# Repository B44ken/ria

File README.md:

# ria

ria is a small wheeled biped built for jumping and fast ground motion.

### bom

- 2x 5010 260kv bldc
- 2x gbm2804 145kv bldc
- 2x sg90 servo
- 4x as5600
- funfly 1300 4s lipo
- m2, m3 screws
- 6x 693zz bearings (planet gears)
- 2x 687zz bearings (knee sprockets)
- 2x gt3 300 mm closed belt

### specs
- 10:1 two stage knee transmission
- custom pcb
- 100mm upper and lower legs
- 720g mass
  - 150g/side motors, 200g plastic, 150g battery, 70g everything else
- 20cm jump height, 30kmh top speed (tentative, accurate-ish)

# printed parts
ria is built mostly from parts designed in cadquery. nearly every part has a flat face so it should be easy to 3d print. you'll also need some m3 screws of various sizes and a handful of bearings.

```bash
cd models
python3 main.py
```

# pcb
the pcb is the most expensive part of the design, at roughly $100 (from jlcpcb assembly). i built it in backplane. the kicad project is at `pcb/ria.kicad_pro`

# software
ria is trained and driven in [botblocks.dev](https://botblocks.dev)

```bash
cd software
botblocks import robot bot.json --save $MY_FORK/robot
botblocks run drive.py
```

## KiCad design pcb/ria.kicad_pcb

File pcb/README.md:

# pcb

open `ria.kicad_pro` in kicad or backplane. edit `ria.kicad_pcb` and `ria.kicad_sch` directly. the local symbols, footprints, library tables and `3dmodels/` travel with the project; `ts-pcb/` retains the original tscircuit source and generated outputs.

the sensorless revision uses a doit esps3-32-n4 module with 4mb flash, four drv8316ctrgfr motor drivers, an icm-42688-p imu, usb-c data and a vertical xt60 battery input. the four encoder headers and their pullups are removed. two measured phase currents per motor give eight adc channels; the third phase current is reconstructed from their sum. motor phase outputs never connect directly to the mcu.

the schematic has 104 components and 93 connected nets. on 2026-10-14, fresh kicad 10.0.6 checks with refilled zones reported zero erc violations, zero pcb errors, zero unrouted connections and zero schematic mismatches. the independent driver audit passed 288 pin/net assertions, and the saved-file verifier passed. fabrication design rules are unchanged. 39 pcb warnings remain: 20 routing-stub/via warnings and 19 silkscreen overlap, edge or mask-clipping warnings. this is a hardware revision; sensorless firmware, continuous motor-current temperature and bench operation are not verified.

the [layout preview](../build/review/current-sensing-65mm/board.png), native reports and verifier output are in `build/review/current-sensing-65mm/`.

run the native checks with kicad's python, which includes `pcbnew` and `wx`, and `kicad-cli` on the path. on this mac:

```sh
export PATH="/Applications/KiCad/KiCad.app/Contents/MacOS:$PATH"
"/Applications/KiCad/KiCad.app/Contents/Frameworks/Python.framework/Versions/3.9/bin/python3.9" verify-kicad.py
"/Applications/KiCad/KiCad.app/Contents/MacOS/kicad-cli" sch erc ria.kicad_sch --format json --exit-code-violations -o /tmp/ria-erc.json
"/Applications/KiCad/KiCad.app/Contents/MacOS/kicad-cli" pcb drc ria.kicad_pcb --schematic-parity --format json --exit-code-violations -o /tmp/ria-drc.json
```

## current sensing and control

the [ti drv8316c datasheet](https://www.ti.com/lit/ds/symlink/drv8316c.pdf) defines the hardware interface and support parts. each drv8316ct uses three pwm inputs without spi. mode connects through 47kΩ to its own avdd, selecting three-pwm control with analog current outputs. the three low-side input pins connect to local avdd, drvoff and vsel_bk connect to ground, and nsleep uses gpio47 with an external pulldown. slew and ocp/sr connect to ground; gain floats for 0.3v/a. each fault output has its own 5.1kΩ pullup to local avdd and a separate mcu input.

soa and sob pass through 330Ω/22pf filters to adc1 inputs. vref connects to the driver's local avdd, giving a zero-current offset of avdd/2, nominally 1.65v. sample only during valid low-side conduction windows synchronized to pwm; these outputs do not continuously measure phase current through every switching state. the 16a hardware overcurrent threshold protects against faults. firmware must impose the intended 2.8a motor-current target rather than treating that threshold as an operating limit.

| motor | pwm a/b/c gpio | current a/b gpio | fault gpio |
| --- | --- | --- | --- |
| 1 | 13 / 14 / 15 | 4 / 5 | 44 |
| 2 | 16 / 17 / 18 | 1 / 2 | 48 |
| 3 | 21 / 35 / 36 | 6 / 7 | 42 |
| 4 | 37 / 38 / 39 | 8 / 9 | 11 |

imu sda/scl move to gpio40/41; its interrupt remains gpio12. battery sensing uses gpio10, a 100kΩ/20kΩ divider and 100nf bypass, giving 2.8v at a 16.8v battery input. gpio3 remains unused because it is a boot strap. use mcpwm for all twelve motor pwm outputs; ledc has eight channels.

each driver has a 47nf 50v charge-pump flying capacitor, 1µf charge-pump reservoir, two 100nf vm bypasses and 10µf 50v local bulk capacitance. local avdd uses a 1µf 50v x7r 0805 capacitor, c28323, selected for ti's effective 0.7–1.3µf requirement at 3.3v. vref shares that bypass; the optional extra capacitor is omitted. each hardware variant's buck converter uses 22Ω from sw_bk to fb_bk and a 22µf 25v 0805 output capacitor. its unloaded output and avdd remain private to that driver, separate from the board's 3.3v supply.

## layout and connectors

the board is 50×65mm, with four copper layers and nominal 1.6mm thickness. components mount on top. the inner layers provide ground and battery distribution; the antenna keepout covers all four copper layers, and the top notch removes pcb material from beneath the antenna. the nominal stackup uses jlc04161h-7628, with 35µm outer and 15.2µm inner copper.

the power connector is a vertical amass xt60pb-m.g.y, c19268037, with its mating face above the board. the [manufacturer drawing](https://www.china-amass.net/uploads/62.XT60PB-M-SPEC-2025V0.pdf) specifies a 15.5×8.1mm housing, 16mm height above the pcb, 7.2mm pin pitch and two 4.6mm pcb holes. the imported footprint was corrected to that drawing; pad 1 is ground and pad 2 is battery. its included 3d model is a simplified housing envelope, not the manufacturer's detailed model.

usb-c is at the bottom centre. the outward-facing motor headers sit at x=78.5/121.5mm, y=91mm, shifted down 2mm to clear the upright xt60. they use 5.08mm-pitch wj2edgr-5.08-03p-14-00a headers, c70914, with 1.7mm drills and 3mm lands. mating wire plugs are wj2edgk-5.08-03p-14-00a, c71371; these are not included in the pcb bom. their housings have no included 3d model, so fit uses the manufacturer's drawing and footprint fabrication outlines. the other two motors use mirrored a/b/c socket columns at 8mm pitch.

the mcu is doit esps3-32-n4, c49164655. its [manufacturer pin table and land drawing](https://atta.szlcsc.com/upload/public/pdf/source/20250610/5E546491D868C5B4673AE97C7A2DC844.pdf) define the module footprint. the ground stencil uses nine 0.9mm openings at 1.4mm pitch with twelve thermal holes between them. the existing wroom model represents its approximate 18×25.5mm envelope. the drv8316c model represents the manufacturer's 5×7mm rgf package.

the driver stencil uses twelve windows with thermal holes in the paste gaps. 58 routed via holes intersect top solder pads and their mask openings, including 24 driver thermal vias; the module also has twelve plated thermal holes. the bottom solder mask covers these holes. filling and capping is an optional assembly-process choice, not a blanket requirement; several terminal-pad vias need assembly review. this sensorless design is separate from the simplified ss6343m candidate in `hardware/oct05-mincaps/`, which has no via-in-pad holes and is the board reviewed and quoted on 2026-10-14.

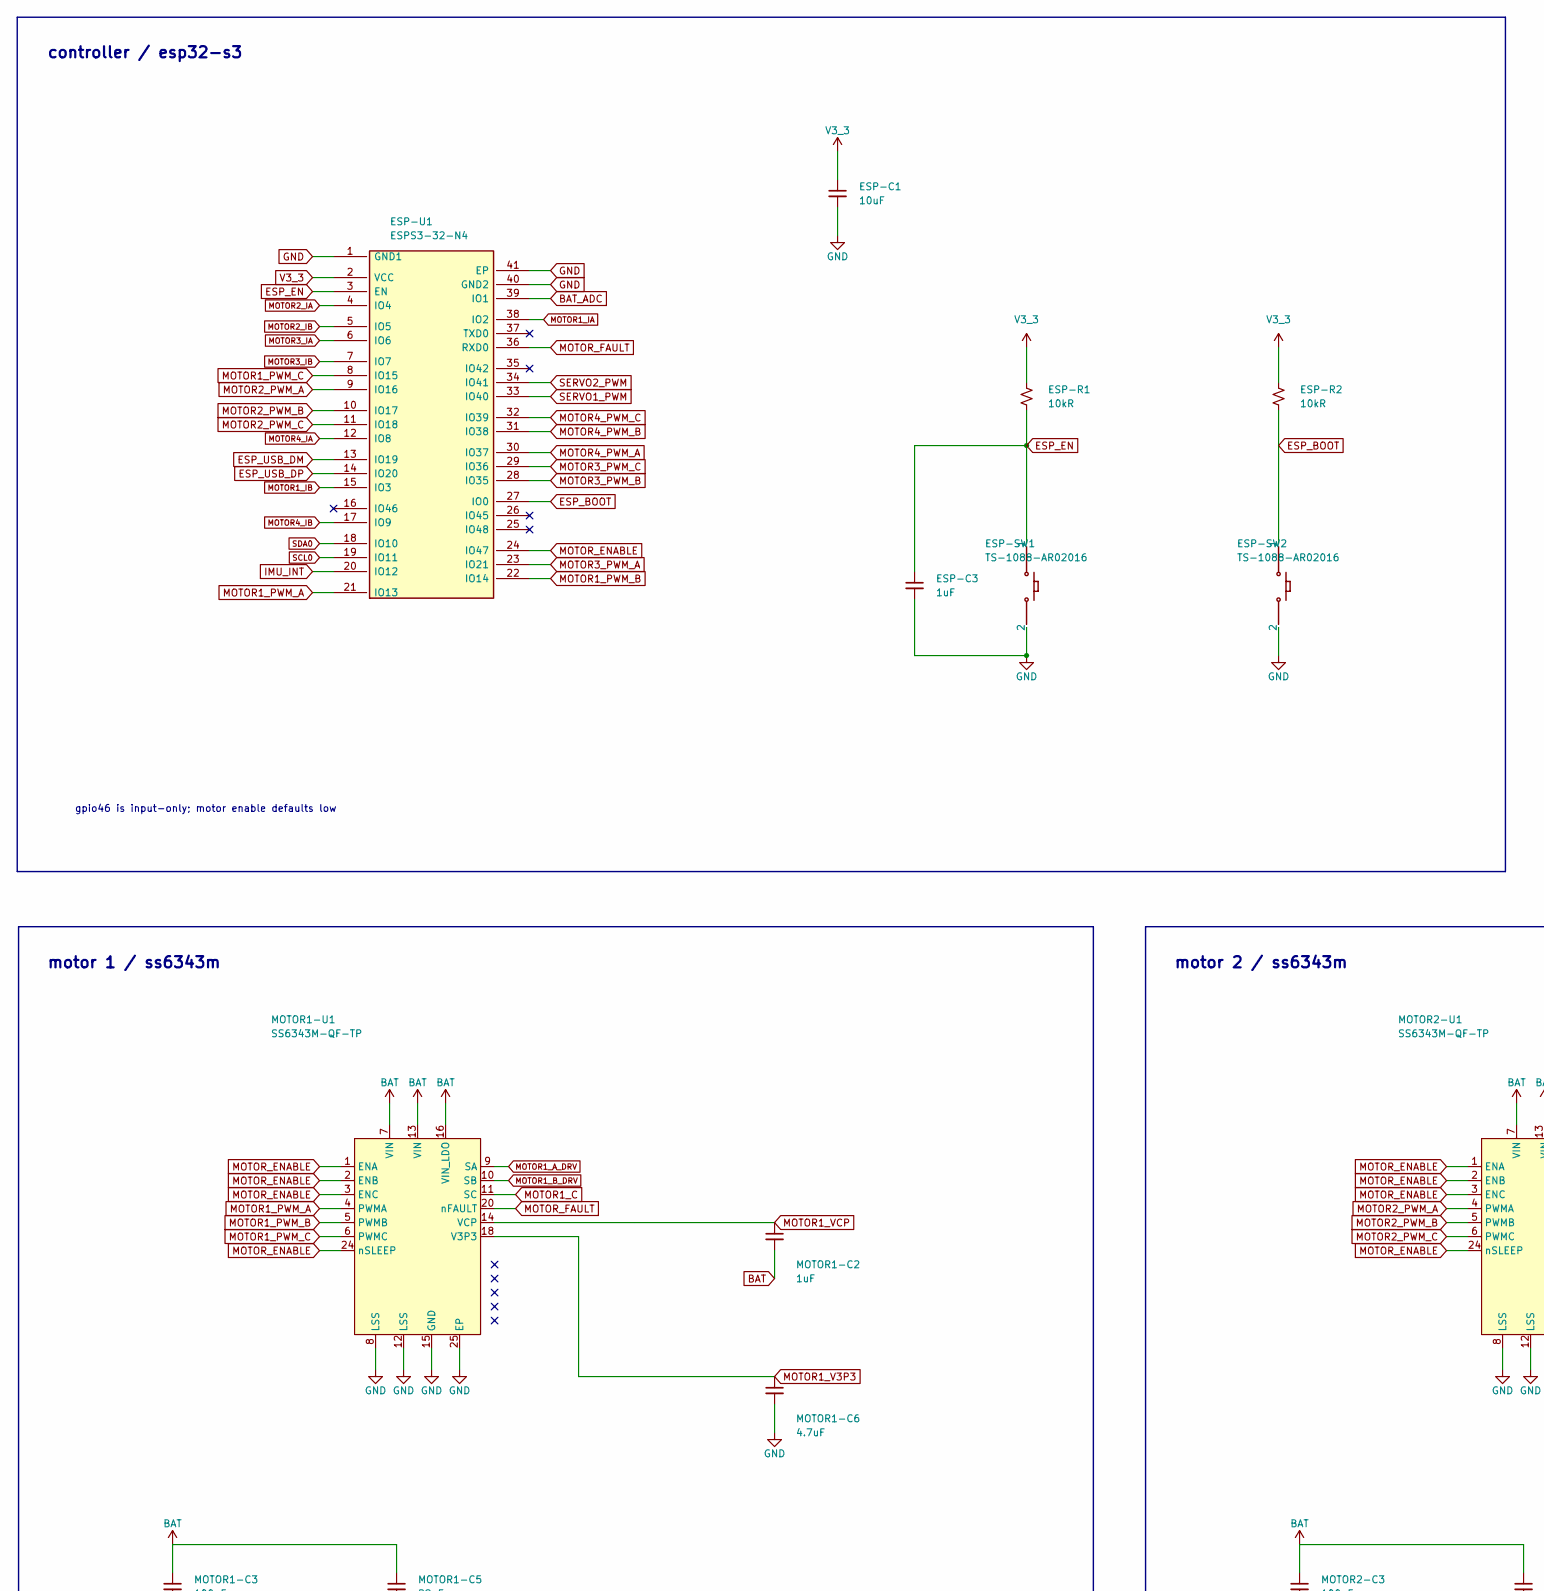
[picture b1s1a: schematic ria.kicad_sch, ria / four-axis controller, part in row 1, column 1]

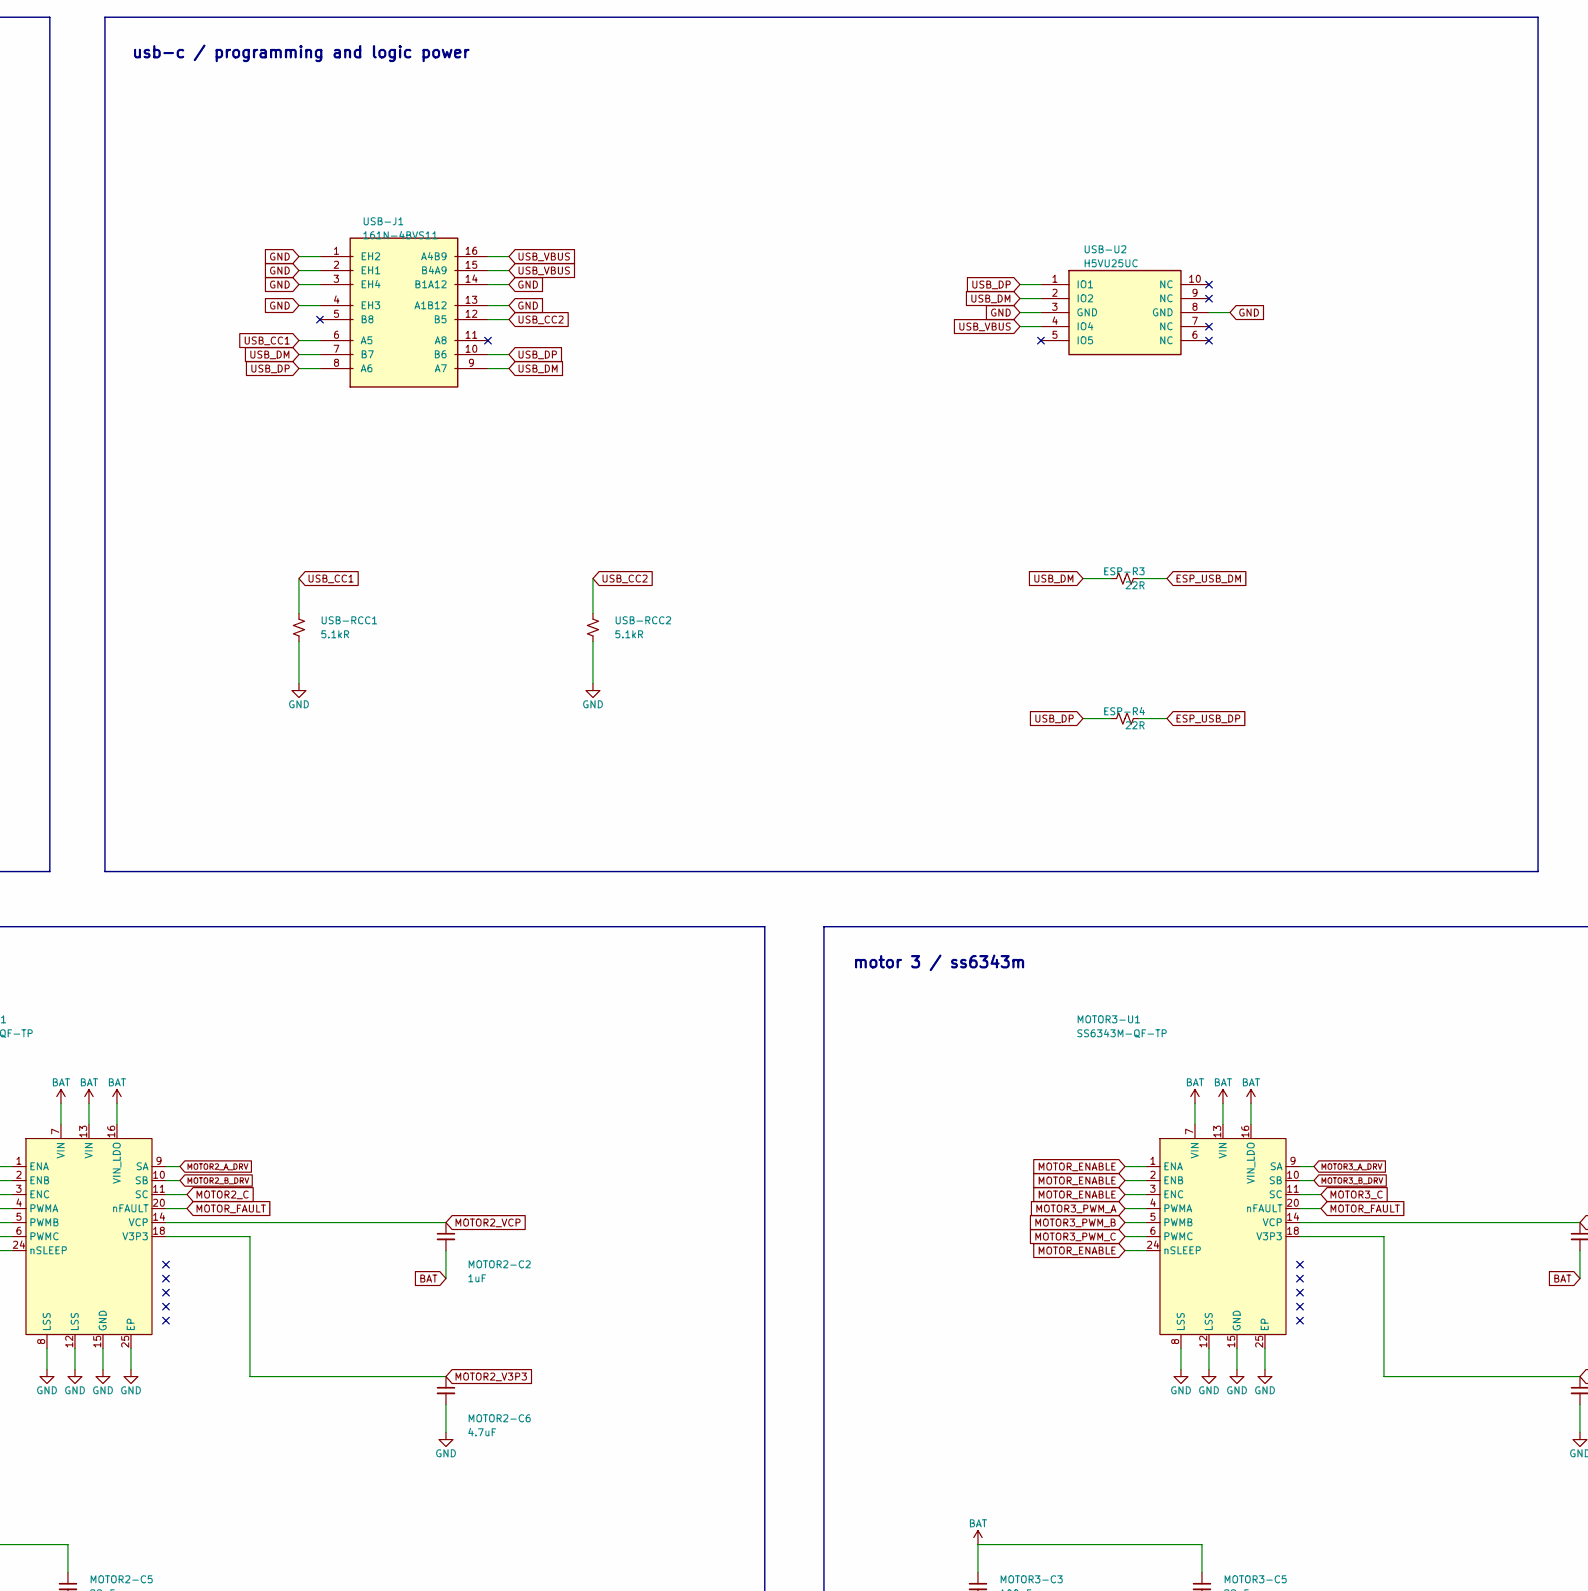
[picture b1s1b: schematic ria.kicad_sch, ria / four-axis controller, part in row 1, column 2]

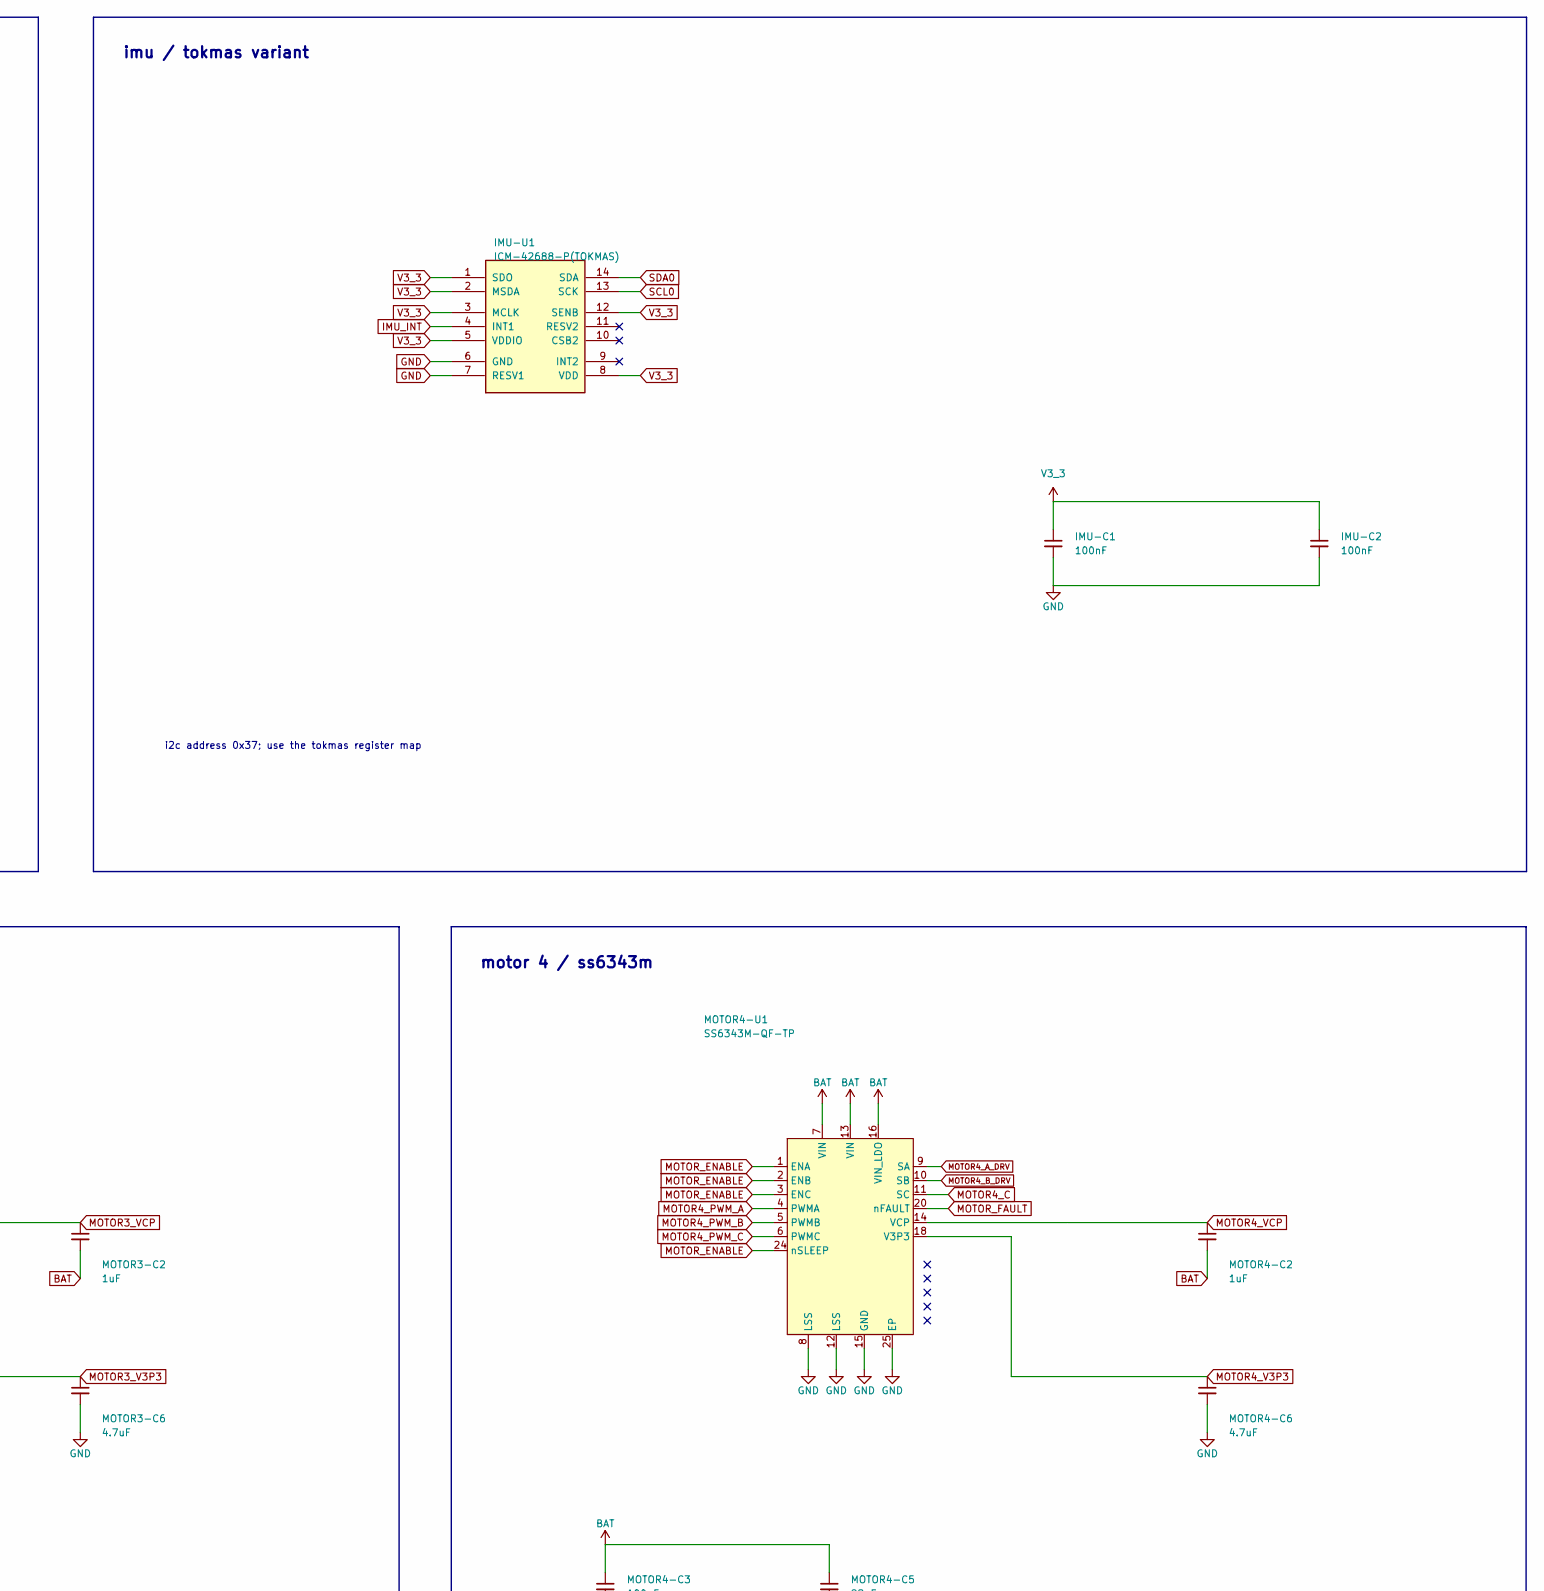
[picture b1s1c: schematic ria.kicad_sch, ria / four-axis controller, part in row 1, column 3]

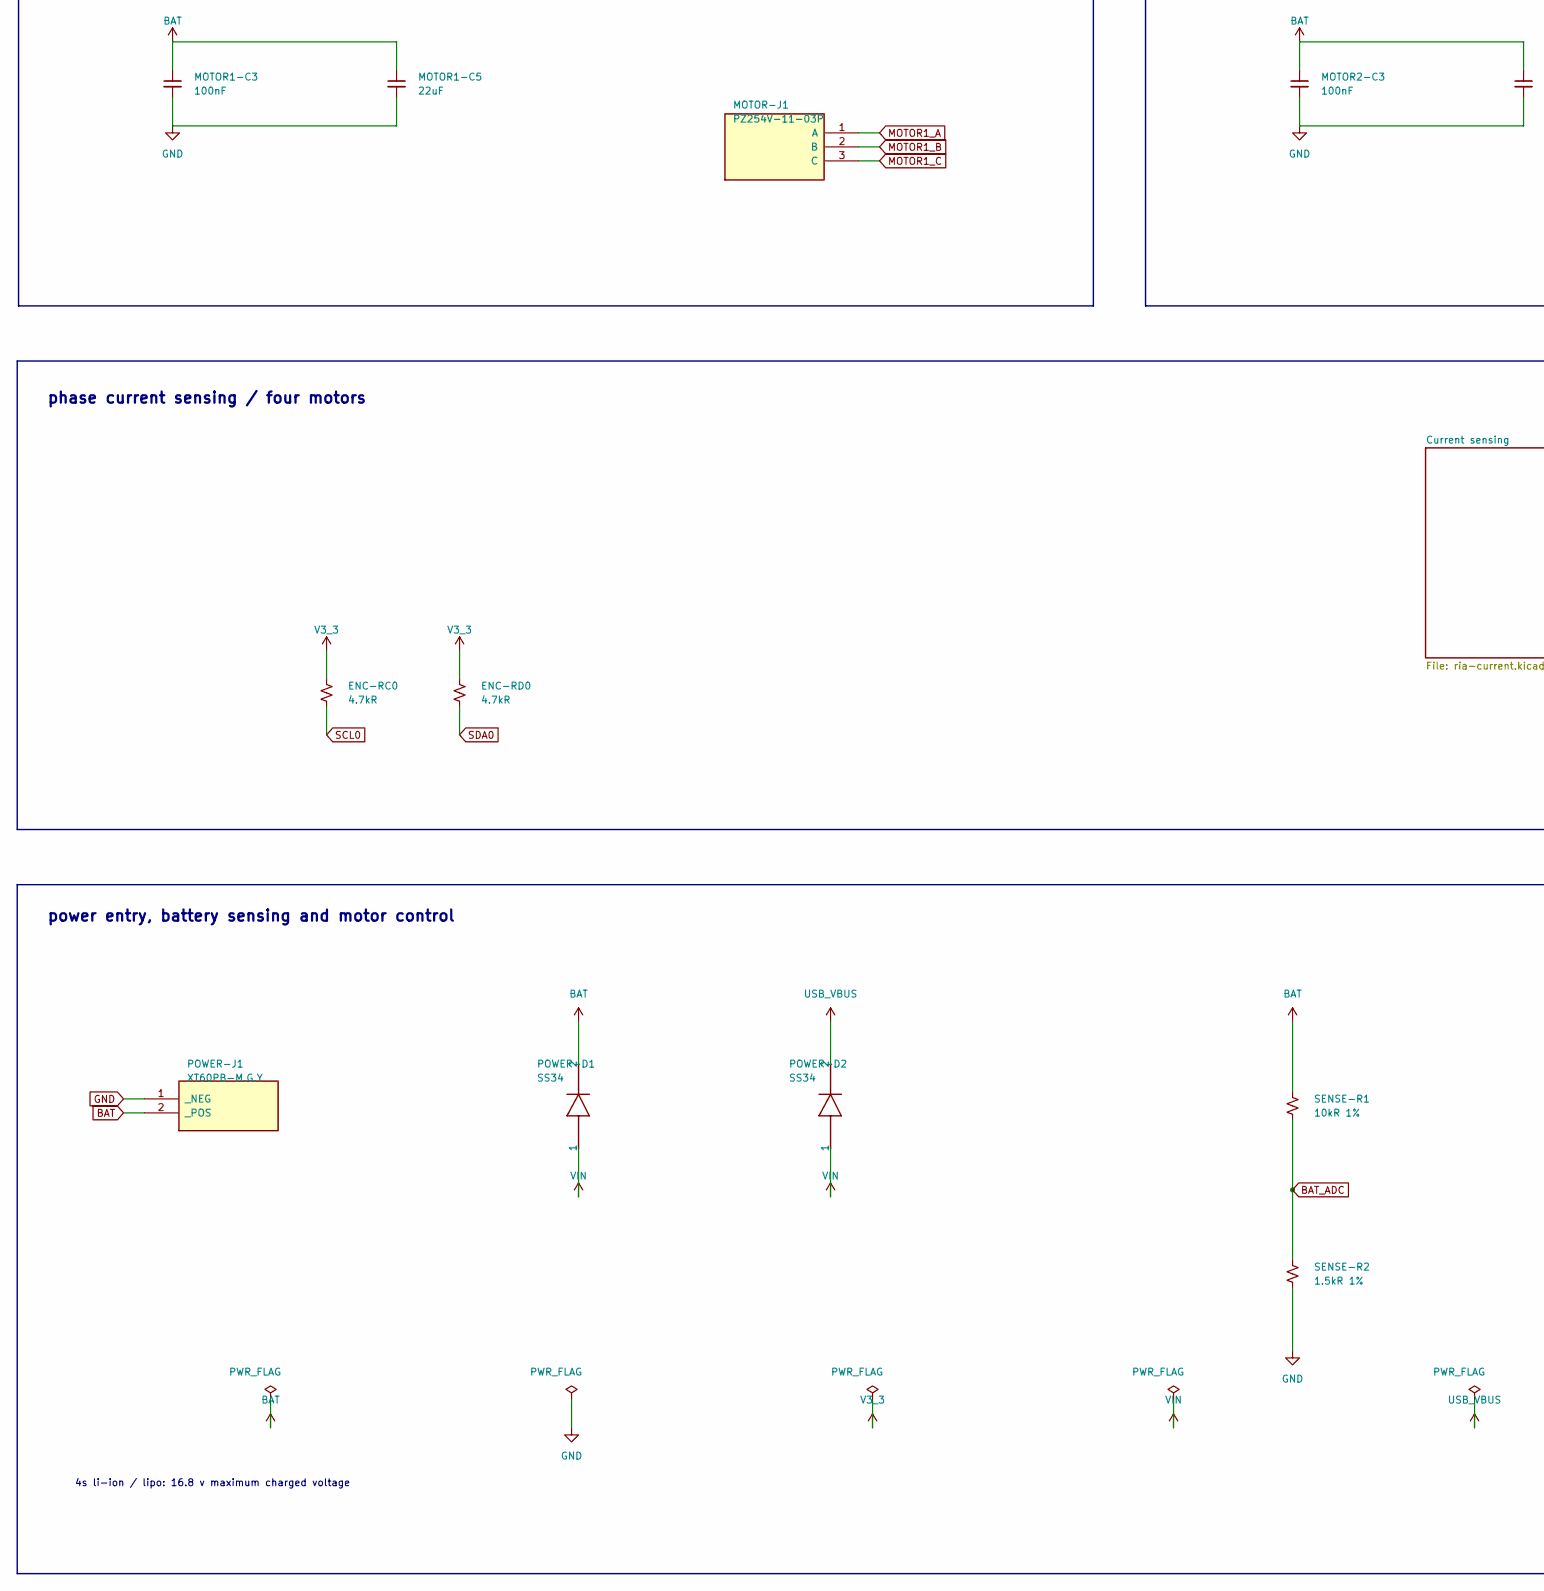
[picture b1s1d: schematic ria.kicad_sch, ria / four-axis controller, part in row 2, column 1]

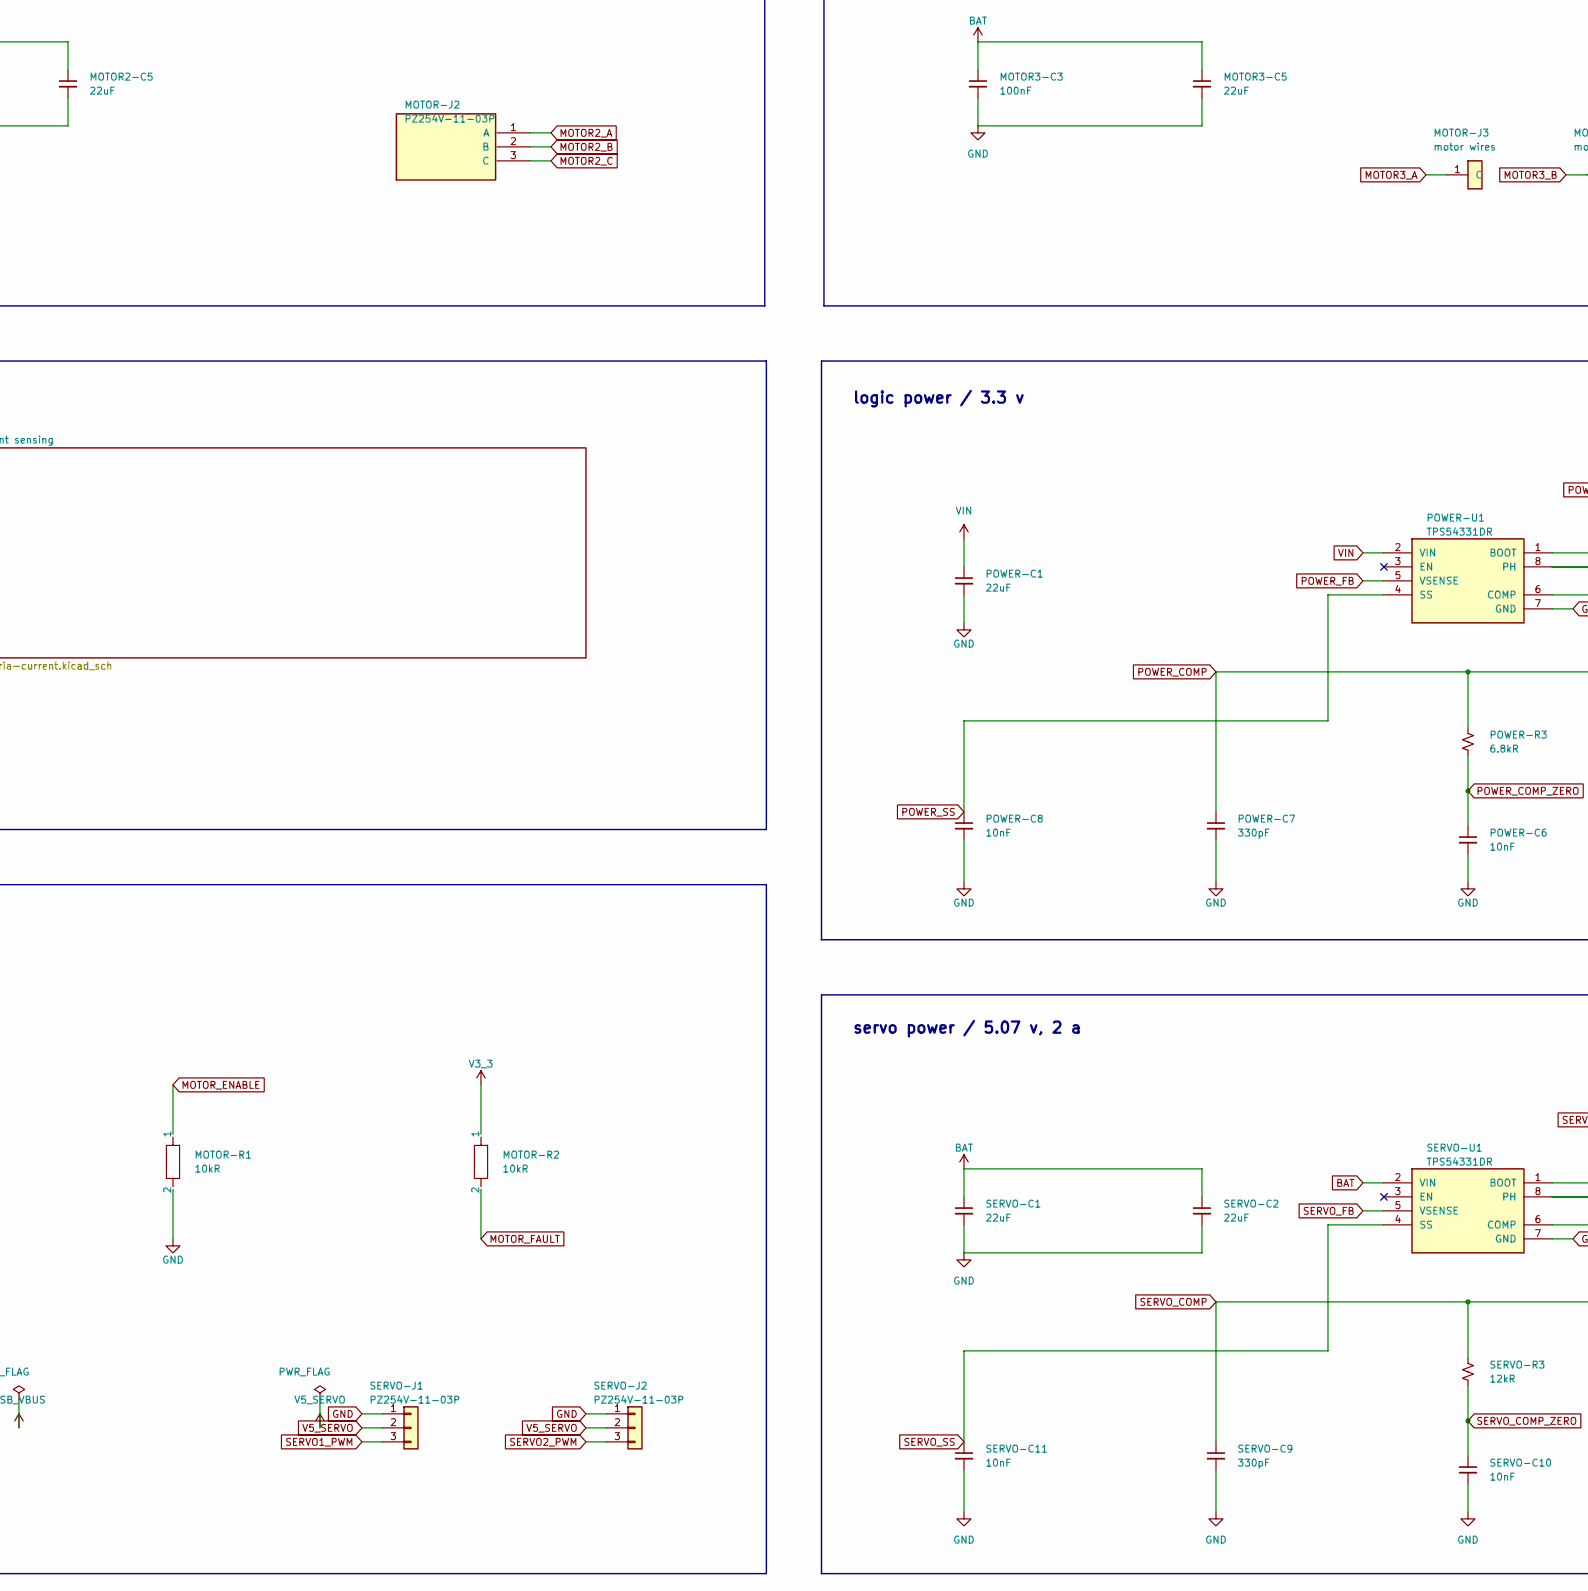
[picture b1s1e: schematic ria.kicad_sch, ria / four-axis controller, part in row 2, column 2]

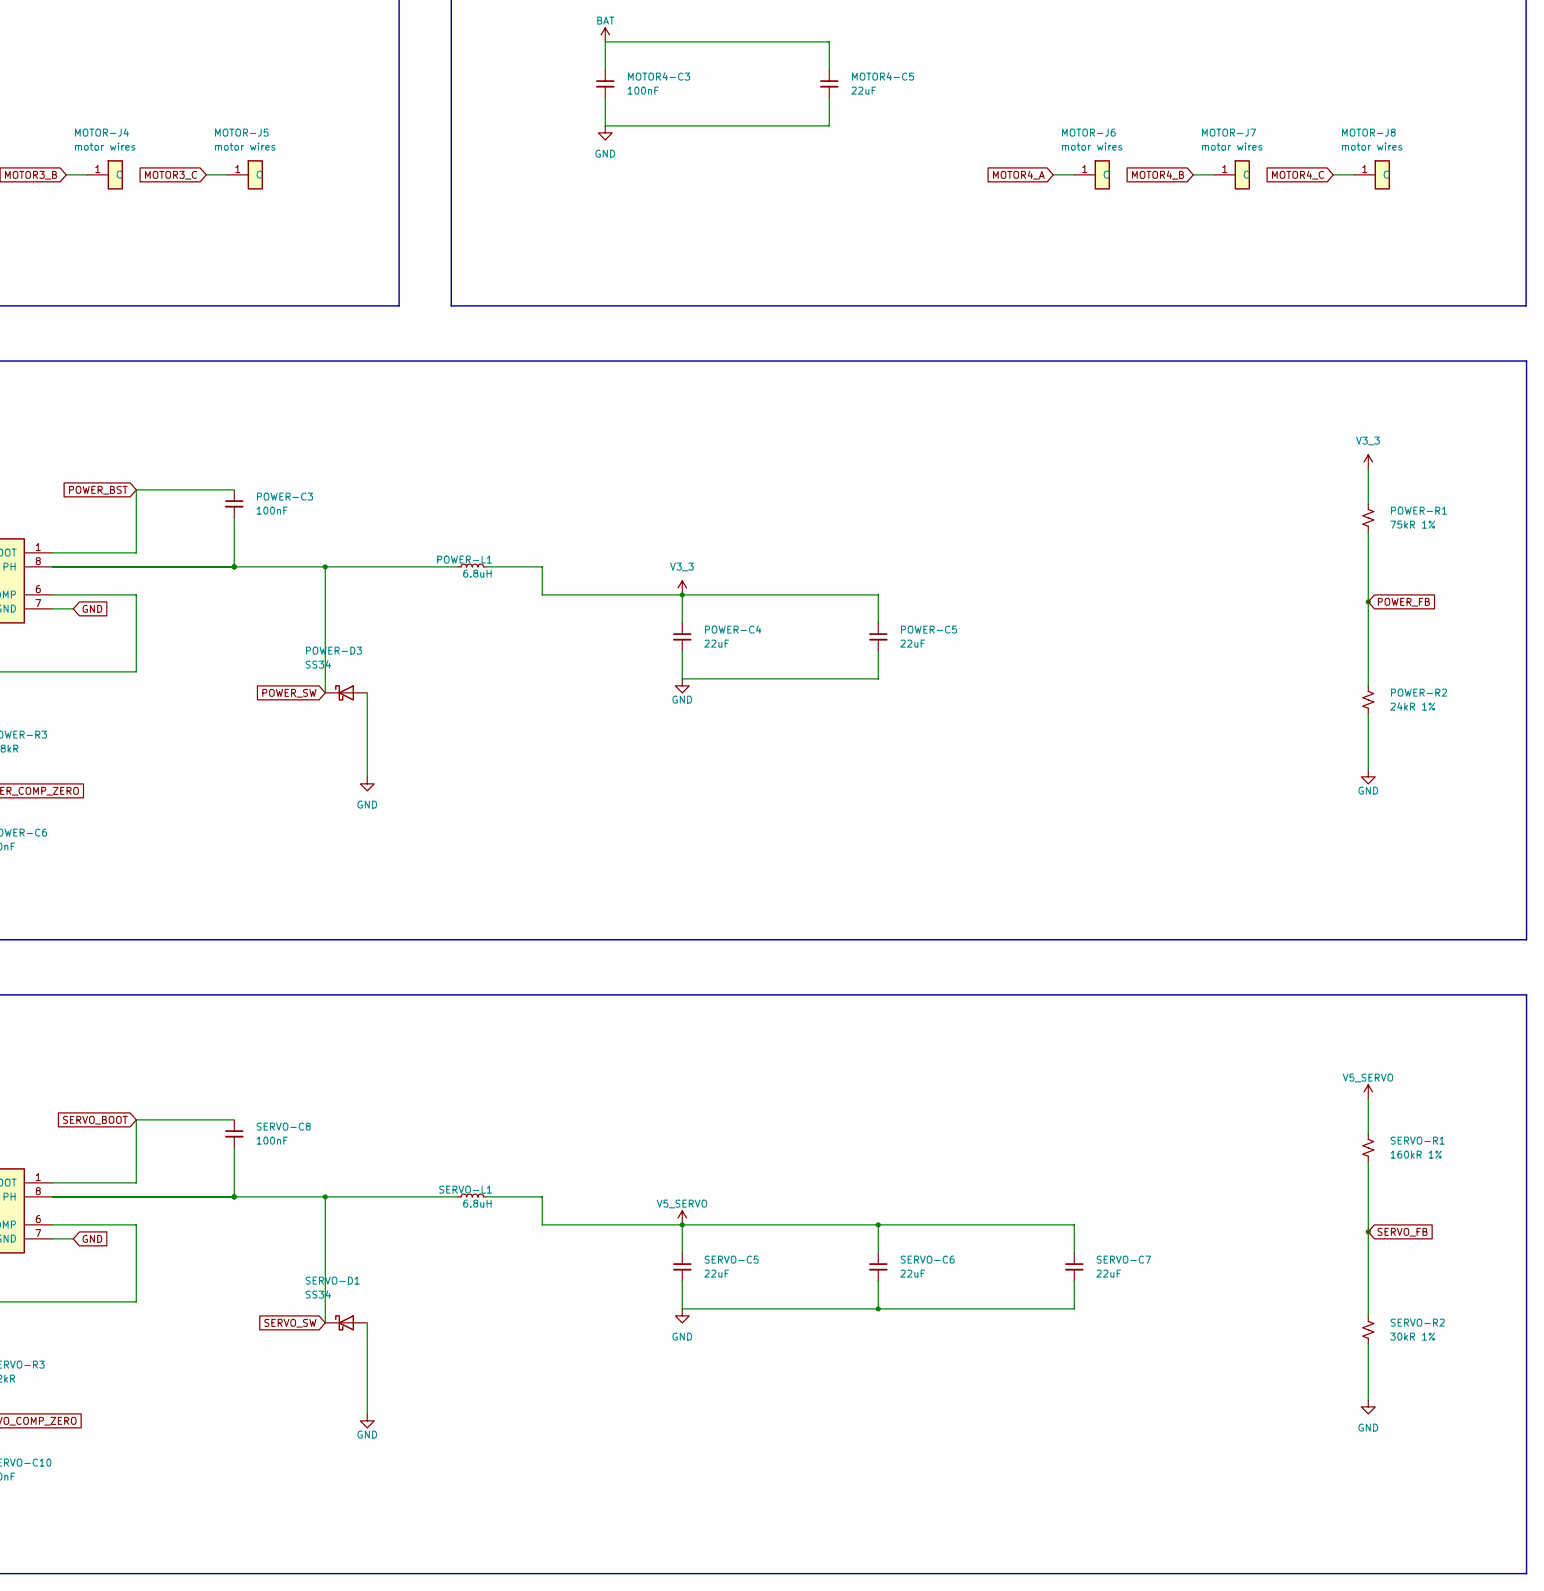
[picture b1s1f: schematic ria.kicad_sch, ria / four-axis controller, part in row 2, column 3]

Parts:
ENC-RC0: 4.7kR; ENC-RC0; MPN 0603WAF4701T5E; LCSC C23162
ENC-RD0: 4.7kR; ENC-RD0; MPN 0603WAF4701T5E; LCSC C23162
ESP-C1: 10uF; ESP-C1; MPN CL21A106KAYNNNE; LCSC C15850
ESP-C3: 1uF; C_0805_2012Metric; MPN CL21B105KBFNNNE; LCSC C28323
ESP-R1: 10kR; ESP-R1; MPN 0603WAF1002T5E; LCSC C25804
ESP-R2: 10kR; ESP-R2; MPN 0603WAF1002T5E; LCSC C25804
ESP-R3: 22R; ESP-R3; MPN 0603WAF220JT5E; LCSC C23345
ESP-R4: 22R; ESP-R4; MPN 0603WAF220JT5E; LCSC C23345
ESP-SW1: TS-1088-AR02016; ESP-SW1; MPN TS-1088-AR02016; LCSC C720477
ESP-SW2: TS-1088-AR02016; ESP-SW2; MPN TS-1088-AR02016; LCSC C720477
ESP-U1: ESPS3-32-N4; ESP-U1; MPN ESPS3-32-N4; LCSC C49164655
IMU-C1: 100nF; IMU-C1; MPN CC0603KRX7R9BB104; LCSC C14663
IMU-C2: 100nF; IMU-C2; MPN CC0603KRX7R9BB104; LCSC C14663
IMU-U1: ICM-42688-P(TOKMAS); IMU-U1; MPN ICM-42688-P(TOKMAS); LCSC C54308212
MOTOR1-C2, MOTOR2-C2, MOTOR3-C2, MOTOR4-C2: 1uF; C_0805_2012Metric; MPN CL21B105KBFNNNE; LCSC C28323
MOTOR1-C3: 100nF; MOTOR1-C3; MPN CC0603KRX7R9BB104; LCSC C14663
MOTOR1-C5, MOTOR2-C5, MOTOR3-C5, MOTOR4-C5: 22uF; C_1206_3216Metric; MPN CL31A226KAHNNNE; LCSC C12891
MOTOR1-C6: 4.7uF; MOTOR1-C6; MPN CL10A475KO8NNNC; LCSC C19666
MOTOR1-U1, MOTOR2-U1, MOTOR3-U1, MOTOR4-U1: SS6343M-QF-TP; MPN SS6343M-QF-TP; LCSC C5370899
MOTOR2-C3: 100nF; MOTOR2-C3; MPN CC0603KRX7R9BB104; LCSC C14663
MOTOR2-C6: 4.7uF; MOTOR2-C6; MPN CL10A475KO8NNNC; LCSC C19666
MOTOR3-C3: 100nF; MOTOR3-C3; MPN CC0603KRX7R9BB104; LCSC C14663
MOTOR3-C6: 4.7uF; MOTOR3-C6; MPN CL10A475KO8NNNC; LCSC C19666
MOTOR4-C3: 100nF; MOTOR4-C3; MPN CC0603KRX7R9BB104; LCSC C14663
MOTOR4-C6: 4.7uF; MOTOR4-C6; MPN CL10A475KO8NNNC; LCSC C19666
MOTOR-J1: PZ254V-11-03P; MOTOR-J1; MPN PZ254V-11-03P; LCSC C2937625
MOTOR-J2: PZ254V-11-03P; MOTOR-J2; MPN PZ254V-11-03P; LCSC C2937625
MOTOR-J3: motor wires; MOTOR-J3A
MOTOR-J4: motor wires; MOTOR-J3B
MOTOR-J5: motor wires; MOTOR-J3C
MOTOR-J6: motor wires; MOTOR-J4A
MOTOR-J7: motor wires; MOTOR-J4B
MOTOR-J8: motor wires; MOTOR-J4C
MOTOR-R1: 10kR; MOTOR-RE; MPN 0603WAF1002T5E; LCSC C25804
MOTOR-R2: 10kR; MOTOR-RS; MPN 0603WAF1002T5E; LCSC C25804
POWER-C1: 22uF; POWER-C1; MPN CL31A226KAHNNNE; LCSC C12891
POWER-C3: 100nF; POWER-C3; MPN CC0603KRX7R9BB104; LCSC C14663
POWER-C4: 22uF; POWER-C4; MPN CL31A226KAHNNNE; LCSC C12891
POWER-C5: 22uF; POWER-C5; MPN CL31A226KAHNNNE; LCSC C12891
POWER-C6: 10nF; POWER-C6; MPN 0603B103K500NT; LCSC C57112
POWER-C7: 330pF; POWER-C7; MPN CL10C331JB8NNNC; LCSC C1664
POWER-C8: 10nF; POWER-C8; MPN 0603B103K500NT; LCSC C57112
POWER-D1: SS34; POWER-D1; MPN SS34; LCSC C8678
POWER-D2: SS34; POWER-D2; MPN SS34; LCSC C8678
POWER-D3: SS34; POWER-D3; MPN SS34; LCSC C8678
POWER-J1: XT60PB-M.G.Y; POWER-J1; MPN XT60PB-M.G.Y; LCSC C19268037
POWER-L1: 6.8uH; POWER-L1; MPN FNR6045S6R8MT; LCSC C168072
POWER-R1: 75kR 1%; POWER-R1; MPN 0603WAF7502T5E; LCSC C23242
POWER-R2: 24kR 1%; POWER-R2; MPN 0603WAF2402T5E; LCSC C23352
POWER-R3: 6.8kR; POWER-R3; MPN 0603WAF6801T5E; LCSC C23212
POWER-U1: TPS54331DR; POWER-U1; MPN TPS54331DR; LCSC C9865
SENSE-R1: 10kR 1%; SENSE-R1; MPN 0603WAF1002T5E; LCSC C25804
SENSE-R2: 1.5kR 1%; SENSE-R2; MPN 0603WAF1501T5E; LCSC C22843
SERVO-C1: 22uF; SERVO-C1; MPN CL31A226KAHNNNE; LCSC C12891
SERVO-C2: 22uF; SERVO-C2; MPN CL31A226KAHNNNE; LCSC C12891
SERVO-C5: 22uF; SERVO-C5; MPN CL31A226KAHNNNE; LCSC C12891
SERVO-C6: 22uF; SERVO-C6; MPN CL31A226KAHNNNE; LCSC C12891
SERVO-C7: 22uF; SERVO-C7; MPN CL31A226KAHNNNE; LCSC C12891
SERVO-C8: 100nF; SERVO-C8; MPN CC0603KRX7R9BB104; LCSC C14663
SERVO-C9: 330pF; SERVO-C9; MPN CL10C331JB8NNNC; LCSC C1664
SERVO-C10: 10nF; SERVO-C10; MPN 0603B103K500NT; LCSC C57112
SERVO-C11: 10nF; SERVO-C11; MPN 0603B103K500NT; LCSC C57112
SERVO-D1: SS34; SERVO-D1; MPN SS34; LCSC C8678
SERVO-J1: PZ254V-11-03P; SERVO-J1; MPN PZ254V-11-03P; LCSC C2937625
SERVO-J2: PZ254V-11-03P; SERVO-J2; MPN PZ254V-11-03P; LCSC C2937625
SERVO-L1: 6.8uH; SERVO-L1; MPN FNR6045S6R8MT; LCSC C168072
SERVO-R1: 160kR 1%; SERVO-R1; MPN 0603WAF1603T5E; LCSC C22813
SERVO-R2: 30kR 1%; SERVO-R2; MPN 0603WAF3002T5E; LCSC C22984
SERVO-R3: 12kR; SERVO-R3; MPN 0603WAF1202T5E; LCSC C22790
SERVO-U1: TPS54331DR; SERVO-U1; MPN TPS54331DR; LCSC C9865
USB-J1: 161N-4BVS11; USB-J1; MPN 161N-4BVS11; LCSC C5440752
USB-RCC1: 5.1kR; USB-RCC1; MPN 0603WAF5101T5E; LCSC C23186
USB-RCC2: 5.1kR; USB-RCC2; MPN 0603WAF5101T5E; LCSC C23186
USB-U2: H5VU25UC; USB-U2; MPN H5VU25UC; LCSC C20615800

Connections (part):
BAT: MOTOR1-C2.2, MOTOR1-C3.1, MOTOR1-C5.1, MOTOR1-U1.7 (VIN), MOTOR1-U1.13 (VIN), MOTOR1-U1.16 (VIN_LDO), MOTOR2-C2.2, MOTOR2-C3.1, MOTOR2-C5.1, MOTOR2-U1.7 (VIN), MOTOR2-U1.13 (VIN), MOTOR2-U1.16 (VIN_LDO), MOTOR3-C2.2, MOTOR3-C3.1, MOTOR3-C5.1, MOTOR3-U1.7 (VIN), MOTOR3-U1.13 (VIN), MOTOR3-U1.16 (VIN_LDO), MOTOR4-C2.2, MOTOR4-C3.1, MOTOR4-C5.1, MOTOR4-U1.7 (VIN), MOTOR4-U1.13 (VIN), MOTOR4-U1.16 (VIN_LDO), POWER-D1.2, POWER-J1.2 (_POS), SENSE-R1.1, SERVO-C1.1, SERVO-C2.1, SERVO-U1.2 (VIN)
BAT_ADC: ESP-U1.39 (IO1), SENSE-R1.2, SENSE-R2.1
ESP_BOOT: ESP-R2.2, ESP-SW2.1, ESP-U1.27 (IO0)
ESP_EN: ESP-C3.1, ESP-R1.2, ESP-SW1.1, ESP-U1.3 (EN)
ESP_USB_DM: ESP-R3.2, ESP-U1.13 (IO19)
ESP_USB_DP: ESP-R4.2, ESP-U1.14 (IO20)
GND: ESP-C1.2, ESP-C3.2, ESP-SW1.2, ESP-SW2.2, ESP-U1.1 (GND1), ESP-U1.40 (GND2), ESP-U1.41 (EP), IMU-C1.2, IMU-C2.2, IMU-U1.6 (GND), IMU-U1.7 (RESV1), MOTOR1-C3.2, MOTOR1-C5.2, MOTOR1-C6.2, MOTOR1-U1.8 (LSS), MOTOR1-U1.12 (LSS), MOTOR1-U1.15 (GND), MOTOR1-U1.25 (EP), MOTOR2-C3.2, MOTOR2-C5.2, MOTOR2-C6.2, MOTOR2-U1.8 (LSS), MOTOR2-U1.12 (LSS), MOTOR2-U1.15 (GND), MOTOR2-U1.25 (EP), MOTOR3-C3.2, MOTOR3-C5.2, MOTOR3-C6.2, MOTOR3-U1.8 (LSS), MOTOR3-U1.12 (LSS), MOTOR3-U1.15 (GND), MOTOR3-U1.25 (EP), MOTOR4-C3.2, MOTOR4-C5.2, MOTOR4-C6.2, MOTOR4-U1.8 (LSS), MOTOR4-U1.12 (LSS), MOTOR4-U1.15 (GND), MOTOR4-U1.25 (EP), MOTOR-R1.2, POWER-C1.2, POWER-C4.2, POWER-C5.2, POWER-C6.2, POWER-C7.2, POWER-C8.2, POWER-D3.2 (A), POWER-J1.1 (_NEG), POWER-R2.2, POWER-U1.7 (GND), SENSE-R2.2, SERVO-C1.2, SERVO-C2.2, SERVO-C5.2, SERVO-C6.2, SERVO-C7.2, SERVO-C9.2, SERVO-C10.2, SERVO-C11.2, SERVO-D1.2 (A), SERVO-J1.1, SERVO-J2.1, SERVO-R2.2, SERVO-U1.7 (GND), USB-J1.1 (EH2), USB-J1.2 (EH1), USB-J1.3 (EH4), USB-J1.4 (EH3), USB-J1.13 (A1B12), USB-J1.14 (B1A12), USB-RCC1.2, USB-RCC2.2, USB-U2.3 (GND), USB-U2.8 (GND); also elsewhere on the board
IMU_INT: ESP-U1.20 (IO12), IMU-U1.4 (INT1)
MOTOR1_A: MOTOR-J1.1 (A); also elsewhere on the board
MOTOR1_A_DRV: MOTOR1-U1.9 (SA); also elsewhere on the board
MOTOR1_B: MOTOR-J1.2 (B); also elsewhere on the board
MOTOR1_B_DRV: MOTOR1-U1.10 (SB); also elsewhere on the board
MOTOR1_C: MOTOR1-U1.11 (SC), MOTOR-J1.3 (C)
MOTOR1_IA: ESP-U1.38 (IO2); also elsewhere on the board
MOTOR1_IB: ESP-U1.15 (IO3); also elsewhere on the board
MOTOR1_PWM_A: ESP-U1.21 (IO13), MOTOR1-U1.4 (PWMA)
MOTOR1_PWM_B: ESP-U1.22 (IO14), MOTOR1-U1.5 (PWMB)
MOTOR1_PWM_C: ESP-U1.8 (IO15), MOTOR1-U1.6 (PWMC)
MOTOR1_V3P3: MOTOR1-C6.1, MOTOR1-U1.18 (V3P3)
MOTOR1_VCP: MOTOR1-C2.1, MOTOR1-U1.14 (VCP)
MOTOR2_A: MOTOR-J2.1 (A); also elsewhere on the board
MOTOR2_A_DRV: MOTOR2-U1.9 (SA); also elsewhere on the board
MOTOR2_B: MOTOR-J2.2 (B); also elsewhere on the board
MOTOR2_B_DRV: MOTOR2-U1.10 (SB); also elsewhere on the board
MOTOR2_C: MOTOR2-U1.11 (SC), MOTOR-J2.3 (C)
MOTOR2_IA: ESP-U1.4 (IO4); also elsewhere on the board
MOTOR2_IB: ESP-U1.5 (IO5); also elsewhere on the board
MOTOR2_PWM_A: ESP-U1.9 (IO16), MOTOR2-U1.4 (PWMA)
MOTOR2_PWM_B: ESP-U1.10 (IO17), MOTOR2-U1.5 (PWMB)
MOTOR2_PWM_C: ESP-U1.11 (IO18), MOTOR2-U1.6 (PWMC)
MOTOR2_V3P3: MOTOR2-C6.1, MOTOR2-U1.18 (V3P3)
MOTOR2_VCP: MOTOR2-C2.1, MOTOR2-U1.14 (VCP)
MOTOR3_A: MOTOR-J3.1 (C_1); also elsewhere on the board
MOTOR3_A_DRV: MOTOR3-U1.9 (SA); also elsewhere on the board
MOTOR3_B: MOTOR-J4.1 (C_1); also elsewhere on the board
MOTOR3_B_DRV: MOTOR3-U1.10 (SB); also elsewhere on the board
MOTOR3_C: MOTOR3-U1.11 (SC), MOTOR-J5.1 (C_1)
MOTOR3_IA: ESP-U1.6 (IO6); also elsewhere on the board
MOTOR3_IB: ESP-U1.7 (IO7); also elsewhere on the board
MOTOR3_PWM_A: ESP-U1.23 (IO21), MOTOR3-U1.4 (PWMA)
MOTOR3_PWM_B: ESP-U1.28 (IO35), MOTOR3-U1.5 (PWMB)
MOTOR3_PWM_C: ESP-U1.29 (IO36), MOTOR3-U1.6 (PWMC)
MOTOR3_V3P3: MOTOR3-C6.1, MOTOR3-U1.18 (V3P3)
MOTOR3_VCP: MOTOR3-C2.1, MOTOR3-U1.14 (VCP)
MOTOR4_A: MOTOR-J6.1 (C_1); also elsewhere on the board
MOTOR4_A_DRV: MOTOR4-U1.9 (SA); also elsewhere on the board
MOTOR4_B: MOTOR-J7.1 (C_1); also elsewhere on the board
MOTOR4_B_DRV: MOTOR4-U1.10 (SB); also elsewhere on the board
MOTOR4_C: MOTOR4-U1.11 (SC), MOTOR-J8.1 (C_1)
MOTOR4_IA: ESP-U1.12 (IO8); also elsewhere on the board
MOTOR4_IB: ESP-U1.17 (IO9); also elsewhere on the board
MOTOR4_PWM_A: ESP-U1.30 (IO37), MOTOR4-U1.4 (PWMA)
MOTOR4_PWM_B: ESP-U1.31 (IO38), MOTOR4-U1.5 (PWMB)
MOTOR4_PWM_C: ESP-U1.32 (IO39), MOTOR4-U1.6 (PWMC)
MOTOR4_V3P3: MOTOR4-C6.1, MOTOR4-U1.18 (V3P3)
MOTOR4_VCP: MOTOR4-C2.1, MOTOR4-U1.14 (VCP)
MOTOR_ENABLE: ESP-U1.24 (IO47), MOTOR1-U1.1 (ENA), MOTOR1-U1.2 (ENB), MOTOR1-U1.3 (ENC), MOTOR1-U1.24 (nSLEEP), MOTOR2-U1.1 (ENA), MOTOR2-U1.2 (ENB), MOTOR2-U1.3 (ENC), MOTOR2-U1.24 (nSLEEP), MOTOR3-U1.1 (ENA), MOTOR3-U1.2 (ENB), MOTOR3-U1.3 (ENC), MOTOR3-U1.24 (nSLEEP), MOTOR4-U1.1 (ENA), MOTOR4-U1.2 (ENB), MOTOR4-U1.3 (ENC), MOTOR4-U1.24 (nSLEEP), MOTOR-R1.1
MOTOR_FAULT: ESP-U1.36 (RXD0), MOTOR1-U1.20 (nFAULT), MOTOR2-U1.20 (nFAULT), MOTOR3-U1.20 (nFAULT), MOTOR4-U1.20 (nFAULT), MOTOR-R2.2
POWER_BST: POWER-C3.1, POWER-U1.1 (BOOT)
POWER_COMP: POWER-C7.1, POWER-R3.1, POWER-U1.6 (COMP)
POWER_COMP_ZERO: POWER-C6.1, POWER-R3.2
POWER_FB: POWER-R1.2, POWER-R2.1, POWER-U1.5 (VSENSE)
POWER_SS: POWER-C8.1, POWER-U1.4 (SS)
POWER_SW: POWER-C3.2, POWER-D3.1 (K), POWER-L1.1, POWER-U1.8 (PH)
SCL0: ENC-RC0.2, ESP-U1.19 (IO11), IMU-U1.13 (SCK)
SDA0: ENC-RD0.2, ESP-U1.18 (IO10), IMU-U1.14 (SDA)
SERVO1_PWM: ESP-U1.33 (IO40), SERVO-J1.3
SERVO2_PWM: ESP-U1.34 (IO41), SERVO-J2.3
SERVO_BOOT: SERVO-C8.1, SERVO-U1.1 (BOOT)
SERVO_COMP: SERVO-C9.1, SERVO-R3.1, SERVO-U1.6 (COMP)
SERVO_COMP_ZERO: SERVO-C10.1, SERVO-R3.2
SERVO_FB: SERVO-R1.2, SERVO-R2.1, SERVO-U1.5 (VSENSE)
SERVO_SS: SERVO-C11.1, SERVO-U1.4 (SS)
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
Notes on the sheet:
4s li-ion / lipo: 16.8 v maximum charged voltage
controller / esp32-s3
usb-c / programming and logic power
imu / tokmas variant
motor 2 / ss6343m
i2c address 0x37; use the tokmas register map
logic power / 3.3 v
motor 3 / ss6343m
motor 1 / ss6343m
gpio46 is input-only; motor enable defaults low
motor 4 / ss6343m
servo power / 5.07 v, 2 a
power entry, battery sensing and motor control
phase current sensing / four motors
